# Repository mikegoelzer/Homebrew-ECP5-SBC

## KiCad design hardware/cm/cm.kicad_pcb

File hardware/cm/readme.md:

# Compute Module

The Compute Module (CM) is the heart of the computer.  It has the two things that every computer needs:  a processor and memory.  

### Features

- ECP5U 85K FPGA
- 1.1V, 2.5V and 3.3V buck regulators for the FPGA's voltage rails
- Supply sequencer to bring voltage rails up and down "correctly" (see below)
- 16MB DRAM
- 25MHz oscillator
- Bitstream SPI flash chip
- 100-pin Hirose DF13 snap-in connectors on the bottom

### Power

The Compute Module is powered by a 5V input.  The 1.1V and 2.5V and 3.3V rails are produced by three TI buck regulators.

The ECP5 should not require a rail sequencer, but I included one (based on a design borrowed from Trellis Board) because I've seen other ECP5 boards get into weird states that seem like they may be caused by rail ramp rate problems.  Thus, the rail sequencing complies strictly with the ECP5's datasheet, at a cost of two extra chips.

### Electrical and Mechanical Connections

The basic idea with the CM is that you use it by snapping it into some larger board -- in my case, the [the motherboard](../motherboard/readme.md) in this repo.  This is the purpose of the two 100-pin Hirose DF13 male connectors on the bottom of the CM.  Everything, even power andJTAG, is brought out solely through these connectors.

The connectors and overall size and shape were inspired by the Raspberry Pi Compute Module 3 (CM3).  I wasn't able to maintain the same pinout as the Pi CM3 because I needed to bring out more IOs and wanted to run off a 5V input.

### Clock Speed

The FPGA includes several PLLs, so the 25 MHz oscillator in this circuit enables the CPU to run at 100 MHz.  

While the CPU itself would probably run fine at higher clock speeds, the DRAM is rated for a maximum speed of 133 MHz.  The memory controller is simplified considerably when you can get results back from DRAM in one clock cycle, so I just run everything in a single 100 MHz clock domain.

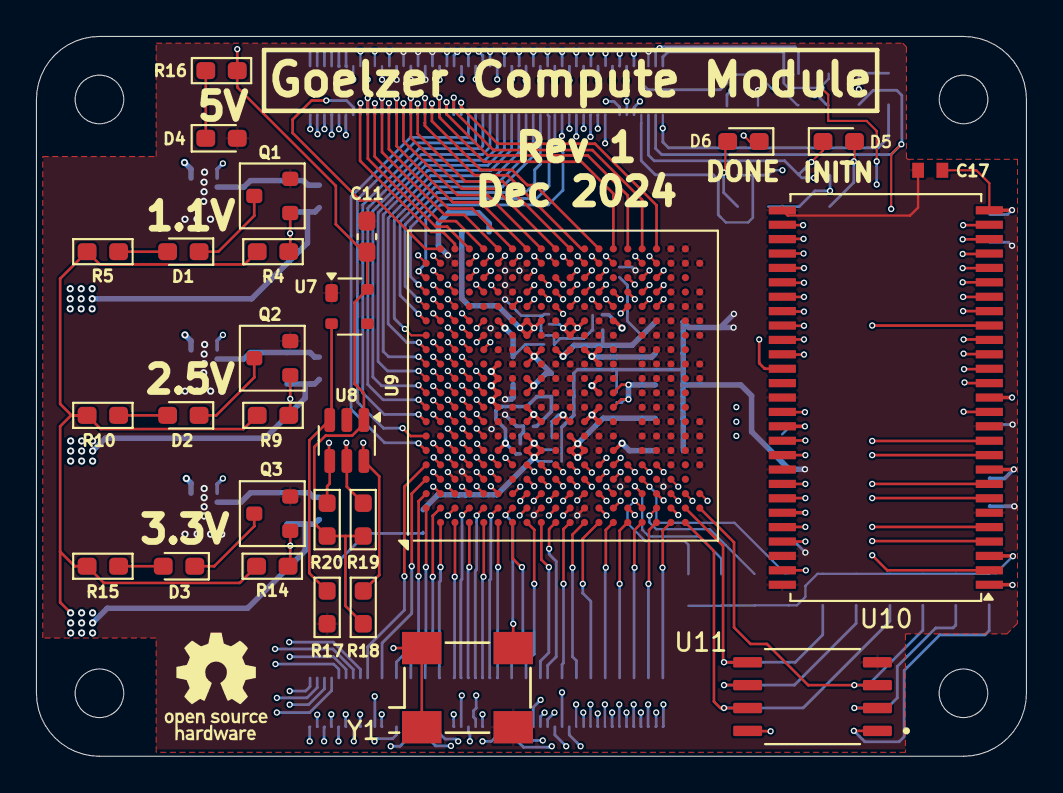
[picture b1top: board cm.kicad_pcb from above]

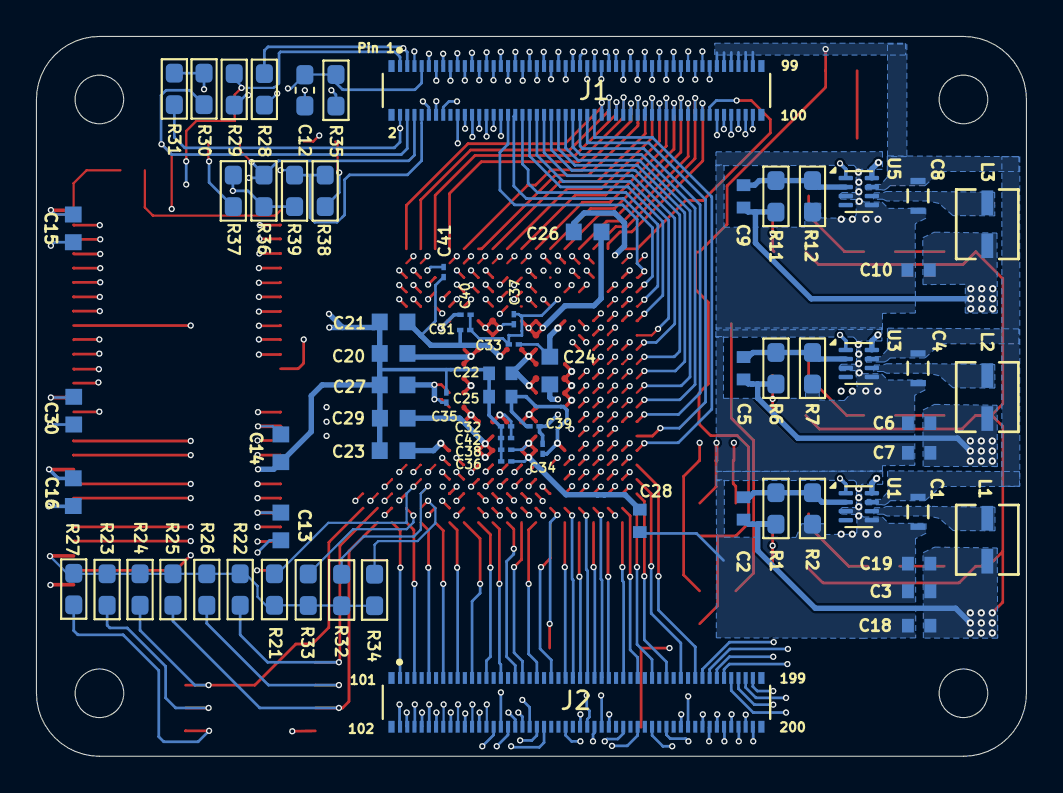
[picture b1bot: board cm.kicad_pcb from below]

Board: 8 copper layers, 55.0 x 40.0 mm, 105 parts (73 on the bottom side), 230 nets.

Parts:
C1, C4, C8: 4.7uF; CAP_1608_TDK-L
C2, C5, C9: 120pF; G-188_MUR-L
C3, C6, C7, C10, C18, C19: 22uF 6.3V; G-188_MUR-L
C11: 0.1uF; C_0603_1608Metric_Pad1.08x0.95mm_HandSolder
C12: 220nF; C_0603_1608Metric_Pad1.08x0.95mm_HandSolder
C13, C14, C15, C16, C20, C21, C23, C24, C26, C27, C29, C30: 22nF; CAPC1608X90N
C17: 2.2uF X5R; CAP_GRM188R61E225KA12D_MUR-L
C22, C25, C28: 2.2uF X7R; G-188_MUR-L
C31, C32, C33, C34, C35, C36, C37, C38, C39, C40, C41, C42: 10nF; G-033_MUR-L
D1, D2, D3, D4, D6: Green; LED_0603_1608Metric_Pad1.05x0.95mm_HandSolder
D5: Red; LED_0603_1608Metric_Pad1.05x0.95mm_HandSolder
H1, H2, H3, H4: MountingHole; MountingHole_2.7mm_M2.5
J1, J2: DF40C-100DP-0.4V_51_; HIROSE_DF40C-100DP-0.4V_51_
L1, L2, L3: 470nH IHLP1212AB; IND_IHLP-1212AB_VIS-L
Q1, Q2, Q3: BSH111; SOT-23
R1: 453k 1%; R_0603_1608Metric_Pad1.05x0.95mm_HandSolder
R2, R7, R12: 100k 1%; R_0603_1608Metric_Pad1.05x0.95mm_HandSolder
R4, R9, R14, R22, R23, R24, R25, R36, R39: 10k; R_0603_1608Metric_Pad1.05x0.95mm_HandSolder
R5, R10, R15, R16, R26: 1k; R_0603_1608Metric_Pad1.05x0.95mm_HandSolder
R6: 316k 1%; R_0603_1608Metric_Pad1.05x0.95mm_HandSolder
R11: 82.5 1%; R_0603_1608Metric_Pad1.05x0.95mm_HandSolder
R17: 100k 1%; R_0603_1608Metric_Pad0.98x0.95mm_HandSolder
R18, R19, R20: 100k; R_0603_1608Metric_Pad0.98x0.95mm_HandSolder
R21, R27, R28, R29, R30, R31, R32, R33, R34, R35: 4.7k; R_0603_1608Metric_Pad1.05x0.95mm_HandSolder
R37, R38: 2.2k; R_0603_1608Metric_Pad1.05x0.95mm_HandSolder
U1, U3, U5: TPS62823DLC; Texas_VSON-HR-8_1.5x2mm_P0.5mm
U7: ADM811MART; SOT-143
U8: LM3880MF-1AA; SOT-23-6
U9: LFE5U-85F-6BG381x; Lattice_caBGA-381_17.0x17.0mm_Layout20x20_P0.8mm_Ball0.4mm_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
U10: MT48LC16M16A2P; TSOP-II-54_22.2x10.16mm_P0.8mm
U11: W25Q128JVSIQ; SOIC127P790X216-8N
Y1: FNETHE025; Crystal_SMD_7050_4Pads

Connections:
+1V1: C9.1, C10.1, C20.1, C21.1, C22.1, C31.1, C32.1, C41.1, C42.1, L3.2, R11.1, U9.H8 (VCC), U9.H9 (VCC), U9.H10 (VCC), U9.H11 (VCC), U9.H12 (VCC), U9.H13 (VCC), U9.J8 (VCC), U9.J13 (VCC), U9.K8 (VCC), U9.K13 (VCC), U9.L8 (VCC), U9.L13 (VCC), U9.M8 (VCC), U9.M13 (VCC), U9.N8 (VCC), U9.N9 (VCC), U9.N10 (VCC), U9.N11 (VCC), U9.N12 (VCC), U9.N13 (VCC)
+2V5: C5.1, C6.1, C7.1, C23.1, C24.1, C25.1, C33.1, C34.1, C39.1, C40.1, L2.2, R6.1, U9.F6 (VCCAUX), U9.F15 (VCCAUX), U9.P6 (VCCAUX), U9.P15 (VCCAUX)
+3V3: C2.1, C3.1, C13.1, C14.1, C15.1, C16.1, C17.1, C18.1, C19.1, C26.1, C27.1, C28.1, C29.1, C30.1, C35.1, C36.1, C37.1, C38.1, D6.1 (K), J1.77, J1.79, J1.81, J1.83, J1.85, J1.87, L1.2, R1.1, R4.2, R5.2, R9.2, R10.2, R14.2, R15.2, R21.2, R22.1, R23.1, R24.1, R25.1, R26.1, R27.2, R29.2, R30.2, R31.2, R32.1, R33.1, R34.1, R35.1, R36.2, R37.2, R39.1, U9.F9 (VCCIO0), U9.F10 (VCCIO0), U9.F11 (VCCIO1), U9.F12 (VCCIO1), U9.H6 (VCCIO7), U9.H7 (VCCIO7), U9.H14 (VCCIO2), U9.H15 (VCCIO2), U9.J6 (VCCIO7), U9.J15 (VCCIO2), U9.L6 (VCCIO6), U9.L7 (VCCIO6), U9.L14 (VCCIO3), U9.L15 (VCCIO3), U9.M6 (VCCIO6), U9.M15 (VCCIO3), U9.P9 (VCCIO8), U9.P10 (VCCIO8), U10.1 (VDD), U10.3 (VDDQ), U10.9 (VDDQ), U10.14 (VDD), U10.27 (VDD), U10.43 (VDDQ), U10.49 (VDDQ), U11.8 (VCC), Y1.1, Y1.4
+5V: C1.1, C4.1, C8.1, C11.1, J1.89, J1.91, J1.93, J1.95, J1.97, J1.99, R16.1, R18.1, R19.1, R20.1, U1.7 (VIN), U3.7 (VIN), U5.7 (VIN), U7.4 (VCC), U8.1 (VCC)
/Flash + JTAG/CS1N: R33.2, U9.U2 (PB13B)
/Flash + JTAG/FLASH_CSN: R27.1, U9.R2 (PB15A), U11.1 (/CS)
/Flash + JTAG/FLASH_IO0: R22.2, U9.W2 (PB11B), U11.5 (DI(IO0))
/Flash + JTAG/FLASH_IO1: R23.2, U9.V2 (PB11A), U11.2 (DO(IO1))
/Flash + JTAG/FLASH_IO2: R24.2, U9.Y2 (PB9B), U11.3 (/WP(IO2))
/Flash + JTAG/FLASH_IO3: R25.2, U9.W1 (PB9A), U11.7 (/HOLD/RESET(IO3))
/Flash + JTAG/FLASH_SCK: R26.2, U9.U3 (CCLK), U11.6 (CLK)
/Flash + JTAG/SN_CSN: R34.2, U9.T2 (PB13A)
/Flash + JTAG/WRITEN: R32.2, U9.T3 (PB18A)
/Hirose Connectors/IO_C2: J2.42, U9.C2 (PL35D)
/Hirose Connectors/IO_C6: J2.22, U9.C6 (PT11A)
/Hirose Connectors/IO_C7: J2.18, U9.C7 (PT11B)
/Hirose Connectors/IO_C8: J2.14, U9.C8 (PT15A)
/Hirose Connectors/IO_C9: J2.10, U9.C9 (PT54A)
/Hirose Connectors/IO_C11: J2.26, U9.C11 (PT65B)
/Hirose Connectors/IO_D3: J2.40, U9.D3 (PL17D)
/Hirose Connectors/IO_D11: J2.6, U9.D11 (PT69A)
/Hirose Connectors/IO_E3: J2.38, U9.E3 (PL20B)
/Hirose Connectors/IO_E7: J1.59, U9.E7 (PT9A)
/Hirose Connectors/IO_F3: J2.28, U9.F3 (PL44B)
/Hirose Connectors/IO_G3: J2.58, U9.G3 (PL44A)
/Hirose Connectors/IO_H2: J2.36, U9.H2 (PL47C)
/Hirose Connectors/IO_H3: J2.54, U9.H3 (PL41D)
/Hirose Connectors/IO_J3: J2.34, U9.J3 (PL50C)
/Hirose Connectors/IO_K2: J2.30, U9.K2 (PL53A)
/Hirose Connectors/IO_K3: J2.32, U9.K3 (PL50D)
/Hirose Connectors/IO_L2: J2.24, U9.L2 (PL86D)
/Hirose Connectors/IO_L3: J2.20, U9.L3 (PL86C)
/Hirose Connectors/IO_M3: J2.16, U9.M3 (PL86B)
/Hirose Connectors/IO_N2: J2.8, U9.N2 (PL89A)
/Hirose Connectors/IO_N3: J2.12, U9.N3 (PL86A)
/Hirose Connectors/IO_N4: J1.14, U9.N4 (PL83C)
/Hirose Connectors/IO_N5: J1.55, U9.N5 (PL83B)
/Hirose Connectors/IO_P1: J2.17, U9.P1 (PL92A)
/Hirose Connectors/IO_P2: J1.10, U9.P2 (PL92B)
/Hirose Connectors/IO_P3: J2.4, U9.P3 (PL92C)
/Hirose Connectors/IO_P4: J1.12, U9.P4 (PL92D)
/Hirose Connectors/IO_P5: J1.51, U9.P5 (PL83D)
/Power/1V1_EN: R18.2, U5.1 (EN), U8.6 (FLAG1)
/Power/1V1_PG: Q3.1 (G), R14.1, U5.8 (PG)
/Power/2V5_EN: R20.2, U3.1 (EN), U8.4 (FLAG3)
/Power/2V5_PG: Q2.1 (G), R9.1, U3.8 (PG)
/Power/3V3_EN: R19.2, U1.1 (EN), U8.5 (FLAG2)
/Power/3V3_PG: Q1.1 (G), R4.1, U1.8 (PG)
/Power/SW_1V1: L3.1, U5.6 (SW)
/Power/SW_2V5: L2.1, U3.6 (SW)
/Power/SW_3V3: L1.1, U1.6 (SW)
CLK_25MHZ: U9.G2 (PL47A), Y1.3
ECP5_DONE: J1.8, R38.2, R39.2, U9.Y3 (DONE)
ECP5_INITN: D5.1 (K), J1.6, R36.1, U9.V3 (~INIT)
ECP5_PRGMN_BTN: C12.1, J1.7, R35.2, U9.W3 (~PROGRAM)
GND: C1.2, C3.2, C4.2, C6.2, C7.2, C8.2, C10.2, C11.2, C12.2, C13.2, C14.2, C15.2, C16.2, C17.2, C18.2, C19.2, C20.2, C21.2, C22.2, C23.2, C24.2, C25.2, C26.2, C27.2, C28.2, C29.2, C30.2, C31.2, C32.2, C33.2, C34.2, C35.2, C36.2, C37.2, C38.2, C39.2, C40.2, C41.2, C42.2, D4.2 (A), J1.5, J1.65, J1.67, J1.69, J1.71, J1.73, J1.75, Q1.2 (S), Q2.2 (S), Q3.2 (S), R2.2, R7.2, R12.2, R17.2, R28.1, U1.3 (AGND), U1.5 (PGND), U3.3 (AGND), U3.5 (PGND), U5.3 (AGND), U5.5 (PGND), U7.1 (GND), U8.2 (GND), U9.B7 (GND), U9.B14 (GND), U9.C19 (GND), U9.D4 (GND), U9.F7 (GND), U9.F8 (GND), U9.F13 (GND), U9.F14 (GND), U9.G4 (GND), U9.G6 (GND), U9.G7 (GND), U9.G8 (GND), U9.G9 (GND), U9.G10 (GND), U9.G11 (GND), U9.G12 (GND), U9.G13 (GND), U9.G14 (GND), U9.G15 (GND), U9.G17 (GND), U9.H19 (GND), U9.J2 (GND), U9.J7 (GND), U9.J9 (GND), U9.J10 (GND), U9.J11 (GND), U9.J12 (GND), U9.J14 (GND), U9.K6 (GND), U9.K7 (GND), U9.K9 (GND), U9.K10 (GND), U9.K11 (GND), U9.K12 (GND), U9.K14 (GND), U9.K15 (GND), U9.L9 (GND), U9.L10 (GND), U9.L11 (GND), U9.L12 (GND), U9.M2 (GND), U9.M7 (GND), U9.M9 (GND), U9.M10 (GND), U9.M11 (GND), U9.M12 (GND), U9.M14 (GND), U9.M16 (GND), U9.N6 (GND), U9.N7 (GND), U9.N14 (GND), U9.N15 (GND), U9.P7 (GND), U9.P8 (GND), U9.P11 (GND), U9.P12 (GND), U9.P13 (GND), U9.P14 (GND), U9.R4 (CFG_2), U9.R19 (GND), U9.T6 (GND), U9.T7 (GND), U9.T8 (GND), U9.T9 (GND), U9.T10 (GND), U9.T11 (GND), U9.T12 (GND), U9.T13 (GND), U9.T14 (GND), U9.T15 (GND), U9.U4 (CFG_0), U9.U6 (GND), U9.U7 (GND), U9.U8 (GND), U9.U9 (GND), U9.U10 (GND), U9.U11 (GND), U9.U12 (GND), U9.U13 (GND), U9.U14 (GND), U9.U15 (GND), U9.V5 (GND), U9.V6 (GND), U9.V7 (GND), U9.V8 (GND), U9.V9 (GND), U9.V10 (GND), U9.V11 (GND), U9.V12 (GND), U9.V13 (GND), U9.V14 (GND), U9.V15 (GND), U9.V16 (GND), U9.V17 (GND), U9.V18 (GND), U9.V19 (GND), U9.V20 (GND), U9.W6 (GND), U9.W7 (GND), U9.W12 (GND), U9.W15 (GND), U9.W16 (GND), U9.W19 (GND), U9.W20 (GND), U9.Y5 (GND), U9.Y6 (GND), U9.Y7 (GND), U9.Y8 (GND), U9.Y11 (GND), U9.Y12 (GND), U9.Y14 (GND), U9.Y15 (GND), U9.Y16 (GND), U9.Y17 (GND), U9.Y19 (GND), U10.6 (VSSQ), U10.12 (VSSQ), U10.28 (VSS), U10.41 (VSS), U10.46 (VSSQ), U10.52 (VSSQ), U10.54 (VSS), U11.4 (GND), Y1.2
IO_A2: J2.71, U9.A2 (PL35A)
IO_A3: J2.75, U9.A3 (PL14C)
IO_A4: J2.79, U9.A4 (PL11A)
IO_A5: J2.83, U9.A5 (PL11B)
IO_A6: J1.56, U9.A6 (PT4A)
IO_A7: J1.54, U9.A7 (PT18A)
IO_A8: J1.52, U9.A8 (PT18B)
IO_A9: J1.50, U9.A9 (PT60A)
IO_A10: J1.48, U9.A10 (PT63A)
IO_A11: J1.46, U9.A11 (PT63B)
IO_A12: J1.44, U9.A12 (PT76A)
IO_A13: J1.42, U9.A13 (PT76B)
IO_A14: J1.40, U9.A14 (PT83A)
IO_A15: J1.38, U9.A15 (PT103A)
IO_A16: J1.36, U9.A16 (PT110A)
IO_A17: J1.34, U9.A17 (PT116A)
IO_A18: J1.32, U9.A18 (PT119A)
IO_A19: J1.100, U9.A19 (PT121A)
IO_B1: J2.63, U9.B1 (PL35B)
IO_B2: J2.67, U9.B2 (PL35C)
IO_B3: J2.52, U9.B3 (PL14D)
IO_B4: J2.90, U9.B4 (PL14B)
IO_B5: J2.64, U9.B5 (PL11C)
IO_B6: J1.41, U9.B6 (PT4B)
IO_B8: J1.39, U9.B8 (PT15B)
IO_B9: J1.37, U9.B9 (PT58A)
IO_B10: J1.35, U9.B10 (PT60B)
IO_B11: J1.33, U9.B11 (PT65A)
IO_B12: J1.31, U9.B12 (PT71A)
IO_B13: J1.29, U9.B13 (PT78A)
IO_B15: J1.27, U9.B15 (PT105A)
IO_B16: J1.25, U9.B16 (PT110B)
IO_B17: J1.23, U9.B17 (PT114A)
IO_B18: J1.21, U9.B18 (PT116B)
IO_B19: J1.98, U9.B19 (PT119B)
IO_B20: J1.88, U9.B20 (PT121B)
IO_C1: J2.59, U9.C1 (PL38A)
IO_C3: J2.48, U9.C3 (PL17C)
IO_C4: J2.88, U9.C4 (PL14A)
IO_C5: J2.94, U9.C5 (PL11D)
IO_C10: J2.2, U9.C10 (PT58B)
IO_C12: J1.9, U9.C12 (PT71B)
IO_C13: J1.11, U9.C13 (PT78B)
IO_C14: J1.13, U9.C14 (PT83B)
IO_C15: J1.15, U9.C15 (PT105B)
IO_C16: J1.17, U9.C16 (PT112A)
IO_C17: J1.19, U9.C17 (PT114B)
IO_C20: J1.86, U9.C20 (PR35A)
IO_D1: J2.55, U9.D1 (PL38B)
IO_D2: J2.57, U9.D2 (PL38C)
IO_D5: J2.68, U9.D5 (PL17B)
IO_D6: J2.72, U9.D6 (PT6B)
IO_D7: J2.96, U9.D7 (PT9B)
IO_D8: J2.100, U9.D8 (PT13B)
IO_D9: J2.95, U9.D9 (PT20A)
IO_D10: J2.99, U9.D10 (PT56A)
IO_D12: J1.96, U9.D12 (PT74A)
IO_D13: J1.94, U9.D13 (PT80A)
IO_D14: J1.90, U9.D14 (PT85A)
IO_D15: J1.92, U9.D15 (PT107A)
IO_D18: J1.28, U9.D18 (PR14A)
IO_D19: J1.26, U9.D19 (PR35B)
IO_D20: J1.84, U9.D20 (PR35C)
IO_E1: J2.51, U9.E1 (PL38D)
IO_E2: J2.53, U9.E2 (PL44D)
IO_E4: J2.86, U9.E4 (PL17A)
IO_E5: J2.80, U9.E5 (PL20C)
IO_E6: J2.76, U9.E6 (PT6A)
IO_E8: J2.98, U9.E8 (PT13A)
IO_E9: J2.85, U9.E9 (PT20B)
IO_E10: J2.93, U9.E10 (PT56B)
IO_E11: J2.97, U9.E11 (PT69B)
IO_E13: J2.89, U9.E13 (PT80B)
IO_E14: J2.87, U9.E14 (PT85B)
IO_E15: J2.91, U9.E15 (PT107B)
IO_E17: J1.30, U9.E17 (PR14B)
IO_E18: J1.24, U9.E18 (PR14C)
IO_E19: J1.22, U9.E19 (PR35D)
IO_E20: J1.82, U9.E20 (PR38A)
IO_F1: J2.47, U9.F1 (PL47B)
IO_F2: J2.49, U9.F2 (PL44C)
IO_F4: J2.56, J2.82, U9.F4 (PL20A)
IO_F5: J2.92, U9.F5 (PL20D)
IO_F17: J1.20, U9.F17 (PR17A)
IO_F19: J1.18, U9.F19 (PR38B)
IO_F20: J1.80, U9.F20 (PR38C)
IO_G1: J2.43, U9.G1 (PL47D)
IO_G5: J2.60, U9.G5 (PL41B)
IO_G20: J1.78, U9.G20 (PR38D)
IO_H1: J2.39, U9.H1 (PL53C)
IO_H20: J1.76, U9.H20 (PR41B)
IO_J1: J2.35, U9.J1 (PL53B)
IO_J19: J1.63, U9.J19 (PR44A)
IO_J20: J1.74, U9.J20 (PR44C)
IO_K1: J2.33, U9.K1 (PL53D)
IO_K19: J1.61, U9.K19 (PR44B)
IO_K20: J1.72, U9.K20 (PR44D)
IO_L1: J2.29, U9.L1 (PL89C)
IO_L19: J1.57, U9.L19 (PR47C)
IO_L20: J1.70, U9.L20 (PR47A)
IO_M1: J2.25, U9.M1 (PL89B)
IO_M19: J1.53, U9.M19 (PR47D)
IO_M20: J1.68, U9.M20 (PR47B)
IO_N1: J2.21, U9.N1 (PL89D)
IO_N19: J1.49, U9.N19 (PR83A)
IO_N20: J1.66, U9.N20 (PR83B)
IO_P19: J1.47, U9.P19 (PR83C)
IO_P20: J1.64, U9.P20 (PR86A)
IO_R1: J2.13, U9.R1 (PB4A)
IO_R20: J1.62, U9.R20 (PR86B)
IO_T1: J2.9, U9.T1 (PB4B)
IO_T19: J1.45, U9.T19 (PR89A)
IO_T20: J1.60, U9.T20 (PR86C)
IO_U1: J2.5, U9.U1 (PB6A)
IO_U19: J1.43, U9.U19 (PR89C)
IO_U20: J1.58, U9.U20 (PR86D)
IO_V1: J2.1, U9.V1 (PB6B)
JTAG_TCK: J1.3, R28.2, U9.T5 (TCK)
JTAG_TDI: J1.4, R30.1, U9.R5 (TDI)
JTAG_TDO: J1.1, R29.1, U9.V4 (TDO)
JTAG_TMS: J1.2, R31.1, U9.U5 (TMS)
unnamed: D1.2 (A), R5.1
unnamed: D1.1 (K), Q1.3 (D)
unnamed: D2.2 (A), R10.1
unnamed: D2.1 (K), Q2.3 (D)
unnamed: D3.2 (A), R15.1
unnamed: D3.1 (K), Q3.3 (D)
unnamed: D4.1 (K), R16.2
unnamed: D5.2 (A), R37.1
unnamed: D6.2 (A), R38.1
unnamed: C2.2, R1.2, R2.1, U1.2 (FB)
unnamed: C5.2, R6.2, R7.1, U3.2 (FB)
unnamed: C9.2, R11.2, R12.1, U5.2 (FB)
unnamed: R17.1, U7.2 (~RESET), U8.3 (EN)
unnamed: R21.1, U9.T4 (CFG_1)
SDRAM_A0: U9.G19 (PR41A), U10.23 (A0)
SDRAM_A1: U9.U16 (PR92C), U10.24 (A1)
SDRAM_A2: U9.U17 (PR92B), U10.25 (A2)
SDRAM_A3: U9.U18 (PR92A), U10.26 (A3)
SDRAM_A4: U9.T18 (PR89D), U10.29 (A4)
SDRAM_A5: U9.T17 (PR92D), U10.30 (A5)
SDRAM_A6: U9.T16 (PR77A), U10.31 (A6)
SDRAM_A7: U9.G16 (PR17C), U10.32 (A7)
SDRAM_A8: U9.H17 (PR20B), U10.33 (A8)
SDRAM_A9: U9.J18 (PR41C), U10.34 (A9)
SDRAM_A10: U9.H18 (PR20A), U10.22 (A10)
SDRAM_A11: U9.P17 (PR53D), U10.35 (A11)
SDRAM_A12: U9.R16 (PR56C), U10.36 (A12)
SDRAM_BA0: U9.J17 (PR20C), U10.20 (BA0)
SDRAM_BA1: U9.H16 (PR17D), U10.21 (BA1)
SDRAM_CASN: U9.K17 (PR29B), U10.17 (~CAS)
SDRAM_CKE: U9.R18 (PR89B), U10.37 (CKE)
SDRAM_CLK: U9.R17 (PR56D), U10.38 (CLK)
SDRAM_CSN: U9.P16 (PR56B), U10.19 (~CS)
SDRAM_D0: U9.M4 (PL83A), U10.2 (DQ0)
SDRAM_D1: U9.N17 (PR56A), U10.4 (DQ1)
SDRAM_D2: U9.N18 (PR53C), U10.5 (DQ2)
SDRAM_D3: U9.M18 (PR50D), U10.7 (DQ3)
SDRAM_D4: U9.L18 (PR50C), U10.8 (DQ4)
SDRAM_D5: U9.M17 (PR53B), U10.10 (DQ5)
SDRAM_D6: U9.N16 (PR53A), U10.11 (DQ6)
SDRAM_D7: U9.L17 (PR50B), U10.13 (DQ7)
SDRAM_D8: U9.H5 (PL41C), U10.42 (DQ8)
SDRAM_D9: U9.J4 (PL50A), U10.44 (DQ9)
SDRAM_D10: U9.J5 (PL50B), U10.45 (DQ10)
SDRAM_D11: U9.K4 (PL56A), U10.47 (DQ11)
SDRAM_D12: U9.K5 (PL56B), U10.48 (DQ12)
SDRAM_D13: U9.L4 (PL56C), U10.50 (DQ13)
SDRAM_D14: U9.L5 (PL56D), U10.51 (DQ14)
SDRAM_D15: U9.M5 (PL77A), U10.53 (DQ15)
SDRAM_DQM0: U9.L16 (PR50A), U10.15 (DQML)
SDRAM_DQM1: U9.H4 (PL41A), U10.39 (DQMH)
SDRAM_RASN: U9.K16 (PR29A), U10.18 (~RAS)
SDRAM_WEN: U9.K18 (PR41D), U10.16 (~WE)

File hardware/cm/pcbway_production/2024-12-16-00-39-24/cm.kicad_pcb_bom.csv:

Designator,Quantity,Value,Footprint,Package,MPN,DNP,Mount_Type,Description,Digikey,Mfgr,PARTREV,STANDARD,MAXIMUM_PACKAGE_HEIGHT,MANUFACTURER,Mouser
"C1, C4, C8",3,4.7uF,CAP_1608_TDK-L,,C1608X6S1C475K080AC,,smt,CAP CER 4.7UF 16V X6S 0603,https://www.digikey.com/en/products/detail/tdk-corporation/C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,TDK,,,,,
"C10, C18, C19, C3, C6, C7",6,22uF 6.3V,G-188_MUR-L,,GRM188R60J226MEA0D,,smt,CAP CER 22UF 6.3V X5R 0603,https://www.digikey.com/en/products/detail/murata-electronic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,Murata Electronics,,,,,
C11,1,0.1uF,C_0603_1608Metric_Pad1.08x0.95mm_HandSolder,,GRM188R72A104KA35D,,smt,Unpolarized capacitor,https://www.digikey.com/en/products/detail/murata-electronic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,Murata,,,,,
C12,1,220nF,C_0603_1608Metric_Pad1.08x0.95mm_HandSolder,,CC0603KRX5R5BB224,,smt,CAP CER 0.22UF 6.3V X5R 0603,https://www.digikey.com/en/products/detail/yageo/CC0603KRX5R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,YAGEO,,,,,
"C13, C14, C15, C16, C20, C21, C23, C24, C26, C27, C29, C30",12,22nF,CAPC1608X90N,,GCM188R72A223KA37J,,smt,CAP CER 0.022UF 100V X7R 0603,https://www.digikey.com/en/products/detail/murata-electronic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,Murata Electronics,,,,,
C17,1,2.2uF X5R,CAP_GRM188R61E225KA12D_MUR-L,,GRM188R61E225KA12D,,smt,CAP CER 2.2UF 25V X5R 0603,https://www.digikey.com/en/products/detail/murata-electronic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,Murata Electronics,,,,,
"C2, C5, C9",3,120pF,G-188_MUR-L,,GRM1885C1H121JA01D,,smt,CAP CER 120PF 50V C0G/NP0 0603,https://www.digikey.com/en/products/detail/murata-electronic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,Murata,,,,,
"C22, C25, C28",3,2.2uF X7R,G-188_MUR-L,,GRM188R71A225KE15D,,smt,CAP CER 2.2UF 10V X7R 0603,https://www.digikey.com/en/products/detail/murata-electronic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,Murata Electronics,,,,,
"C31, C32, C33, C34, C35, C36, C37, C38, C39, C40, C41, C42",12,10nF,G-033_MUR-L,,GRM033R71A103KA01D,,smt,CAP CER 10000PF 10V X7R 0201,https://www.digikey.com/en/products/detail/murata-electronic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,Murata Electronics,,,,,
"D1, D2, D3, D4, D6",5,Green,LED_0603_1608Metric_Pad1.05x0.95mm_HandSolder,,150060VS75000,,smt,Light emitting diode,https://www.digikey.com/en/products/detail/w%C3%BCrth-elektr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,Wurth,,,,,
D5,1,Red,LED_0603_1608Metric_Pad1.05x0.95mm_HandSolder,,150060SS75000,,smt,Light emitting diode,https://www.digikey.com/en/products/detail/w%C3%BCrth-elektr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,Wurth,,,,,
"H1, H2, H3, H4",4,MountingHole,MountingHole_2.7mm_M2.5,,,,tht,Mounting Hole without connection,,,,,,,
"J1, J2",2,DF40C-100DP-0.4V_51_,HIROSE_DF40C-100DP-0.4V_51_,,,,smt,"Hirose DF40 1.5mm stacked, plug (male)",,,8,Manufacturer Recommendations,1.29mm,Hirose,
"L1, L2, L3",3,470nH IHLP1212AB,IND_IHLP-1212AB_VIS-L,,IHLP1212ABERR47M11,,smt,FIXED IND 470NH 6.4A 19.5MOHM SMD,https://www.digikey.com/en/products/detail/vishay-dale/IHLP1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,Vishay Dale,,,,,
"Q1, Q2, Q3",3,BSH111,SOT-23,,BSH111BKR,,smt,"SOT-23 N-MOSFET enchancement mode transistor, 55V, 210mA, 302mW, Alternate KiCAD Library",https://www.digikey.com/en/products/detail/nexperia-usa-inc/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,Nexperia,,,,,
R1,1,453k 1%,R_0603_1608Metric_Pad1.05x0.95mm_HandSolder,,RC0603FR-07453KL,,smt,RES 453K OHM 1% 1/10W 0603,https://www.digikey.com/en/products/detail/yageo/RC0603FR-07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,YAGEO,,,,,
"R10, R15, R16, R26, R5",5,1k,R_0603_1608Metric_Pad1.05x0.95mm_HandSolder,,RC0603FR-071KL,,smt,"Resistor, US symbol",[R5]https://www.digikey.com/en/products/detail/yageo/RC0603FR-07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; [R26]https://www.digikey.com/en/products/detail/yageo/rc0603fr-07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,YAGEO,,,,,
R11,1,82.5 1%,R_0603_1608Metric_Pad1.05x0.95mm_HandSolder,,RC0603FR-0782K5L,,smt,RES 82.5K OHM 1% 1/10W 0603,https://www.digikey.com/en/products/detail/yageo/rc0603fr-07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,YAGEO,,,,,
"R12, R2, R7",3,100k 1%,R_0603_1608Metric_Pad1.05x0.95mm_HandSolder,,RC0603FR-07100KL,,smt,RES 100K OHM 1% 1/10W 0603,https://www.digikey.com/en/products/detail/yageo/RC0603FR-07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,YAGEO,,,,,
"R14, R22, R23, R24, R25, R36, R39, R4, R9",9,10k,R_0603_1608Metric_Pad1.05x0.95mm_HandSolder,,RC0603FR-0710KL,,smt,"Resistor, US symbol",https://www.digikey.com/en/products/detail/yageo/RC0603FR-07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,YAGEO,,,,,
R17,1,100k 1%,R_0603_1608Metric_Pad0.98x0.95mm_HandSolder,,RC0603FR-07100KL,,smt,RES 100K OHM 1% 1/10W 0603,https://www.digikey.com/en/products/detail/yageo/RC0603FR-07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,YAGEO,,,,,
"R18, R19, R20",3,100k,R_0603_1608Metric_Pad0.98x0.95mm_HandSolder,,RC0603FR-07100KL,,smt,RES 100K OHM 1% 1/10W 0603,https://www.digikey.com/en/products/detail/yageo/RC0603FR-07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,YAGEO,,,,,
"R21, R27, R28, R29, R30, R31, R32, R33, R34, R35",10,4.7k,R_0603_1608Metric_Pad1.05x0.95mm_HandSolder,,RC0603FR-074K7L,,smt,"Resistor, US symbol",https://www.digikey.com/en/products/detail/yageo/rc0603fr-07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,YAGEO,,,,,
"R37, R38",2,2.2k,R_0603_1608Metric_Pad1.05x0.95mm_HandSolder,,RC0603FR-072K2L,,smt,"Resistor, US symbol",https://www.digikey.com/en/products/detail/yageo/RC0603FR-07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,YAGEO,,,,,
R6,1,316k 1%,R_0603_1608Metric_Pad1.05x0.95mm_HandSolder,,RC0603FR-07316KL,,smt,RES 316K OHM 1% 1/10W 0603,https://www.digikey.com/en/products/detail/yageo/rc0603fr-07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,YAGEO,,,,,
"U1, U3, U5",3,TPS62823DLC,Texas_VSON-HR-8_1.5x2mm_P0.5mm,,TPS62823DLCR,,smt,"3A Step-Down Converter with DCS-Control, adjustable output, 2.4-5.5V input voltage, QFN-8",https://www.digikey.com/en/products/detail/texas-instruments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,Texas Instruments,,,,,
U10,1,MT48LC16M16A2P,TSOP-II-54_22.2x10.16mm_P0.8mm,,,,smt,"256M – (16M x 16 bit) Synchronous DRAM (SDRAM), TSOP-II-54",https://www.digikey.com/en/products/detail/micron-technology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,,,,,,https://www.mouser.com/ProductDetail/Micron/MT48LC16M16A2P-6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
U11,1,W25Q128JVSIQ,SOIC127P790X216-8N,,,,smt,,,,I,IPC-7351B,2.16 mm,Winbond Electronics,
U7,1,ADM811MART,SOT-143,,ADM811MARTZ-REEL7,,smt,"Power supply supervisor, Manual reset, Threshold 4.38V, SOT-143",https://www.digikey.com/en/products/detail/analog-devices-in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,Analog Devices,,,,,
U8,1,LM3880MF-1AA,SOT-23-6,,LM3880MFX-1AA/NOPB,,smt,"Simple Power Sequencer, SOT-23-6",https://www.digikey.com/en/products/detail/texas-instruments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,Texas Instruments,,,,,
U9,1,LFE5U-85F-6BG381x,Lattice_caBGA-381_17.0x17.0mm_Layout20x20_P0.8mm_Ball0.4mm_Pad0.4mm_NSMD,,,,smt,"ECP5 FPGA, 84K LUTs, 1.2V, BGA-381",,,,,,,
Y1,1,FNETHE025,Crystal_SMD_7050_4Pads,,FNETHE025,,smt,XTAL OSC XO 25.0000MHZ CMOS SMD,https://www.digikey.com/en/products/detail/diodes-incorporat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,Diodes Incorporated,,,,,

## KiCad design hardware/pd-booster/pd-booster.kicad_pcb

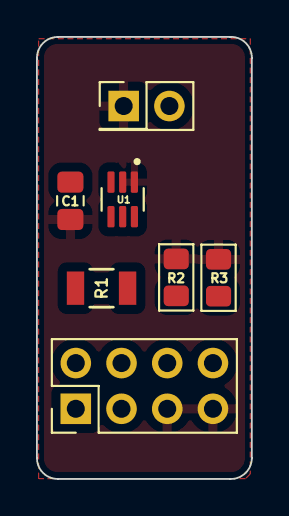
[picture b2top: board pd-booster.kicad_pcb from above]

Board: 2 copper layers, 11.9 x 24.6 mm, 7 parts (0 on the bottom side), 6 nets, no tracks yet.

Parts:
C1: 0.1uF; C_0805_2012Metric_Pad1.18x1.45mm_HandSolder
J1: 2x4 male 0.1"; PinHeader_2x04_P2.54mm_Vertical
J2: PH1RB-02-UA; PinHeader_2x01_P2.54mm_Vertical
R1: 2mΩ 1% 1W; STA_CSNL1206_STP
R2, R3: 5.1k 1%; R_0805_2012Metric_Pad1.15x1.40mm_HandSolder
U1: INA211BIDCKT; SOT65P210X110-6N

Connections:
/5V_OUT: J1.3, J1.4, R1.2, U1.5 (-IN)
/CC1: J1.6, R2.1
/CC2: J1.8, R3.1
/ISENSE: J2.2, U1.6 (OUT)
/VBUS_IN: C1.1, J1.1, J1.2, R1.1, U1.3 (V+), U1.4 (+IN)
GND: C1.2, J1.5, J1.7, J2.1, R2.2, R3.2, U1.1 (REF), U1.2 (GND)

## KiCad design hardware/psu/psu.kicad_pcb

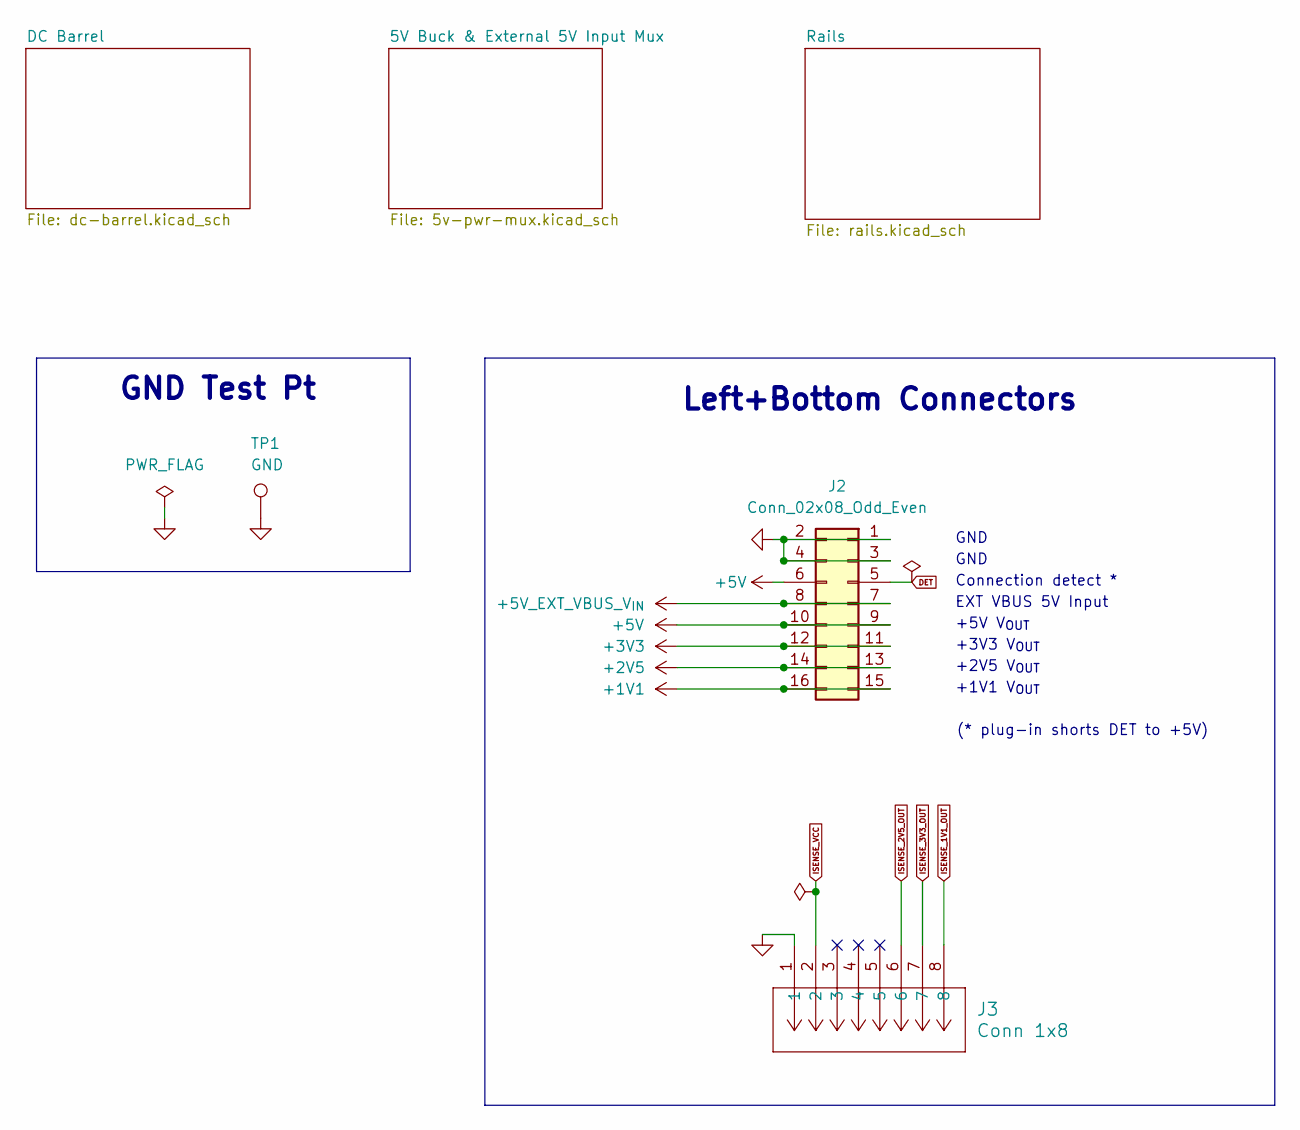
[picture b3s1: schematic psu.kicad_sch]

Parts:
J2: Conn_02x08_Odd_Even; PinSocket_2x08_P2.54mm_Vertical
J3: Conn 1x8; CONN8_61300811121_WRE; MPN 61300811121
TP1: GND; TestPoint_Keystone_5000-5004_Miniature; MPN 5001

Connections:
+1V1: J2.15, J2.16; also elsewhere on the board
+2V5: J2.13, J2.14; also elsewhere on the board
+3V3: J2.11, J2.12; also elsewhere on the board
+5V: J2.6, J2.9, J2.10; also elsewhere on the board
+5V_EXT_VBUS_V_{IN}: J2.7, J2.8; also elsewhere on the board
DET: J2.5; also elsewhere on the board
GND: J2.1, J2.2, J2.3, J2.4, J3.1, TP1.1; also elsewhere on the board
ISENSE_1V1_OUT: J3.8; also elsewhere on the board
ISENSE_2V5_OUT: J3.6; also elsewhere on the board
ISENSE_3V3_OUT: J3.7; also elsewhere on the board
ISENSE_VCC: J3.2; also elsewhere on the board

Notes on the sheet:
GND
Connection detect *
+2V5 V_{OUT}
+5V V_{OUT}
+3V3 V_{OUT}
EXT VBUS 5V Input
(* plug-in shorts DET to +5V)
GND Test Pt
+1V1 V_{OUT}
Left+Bottom Connectors

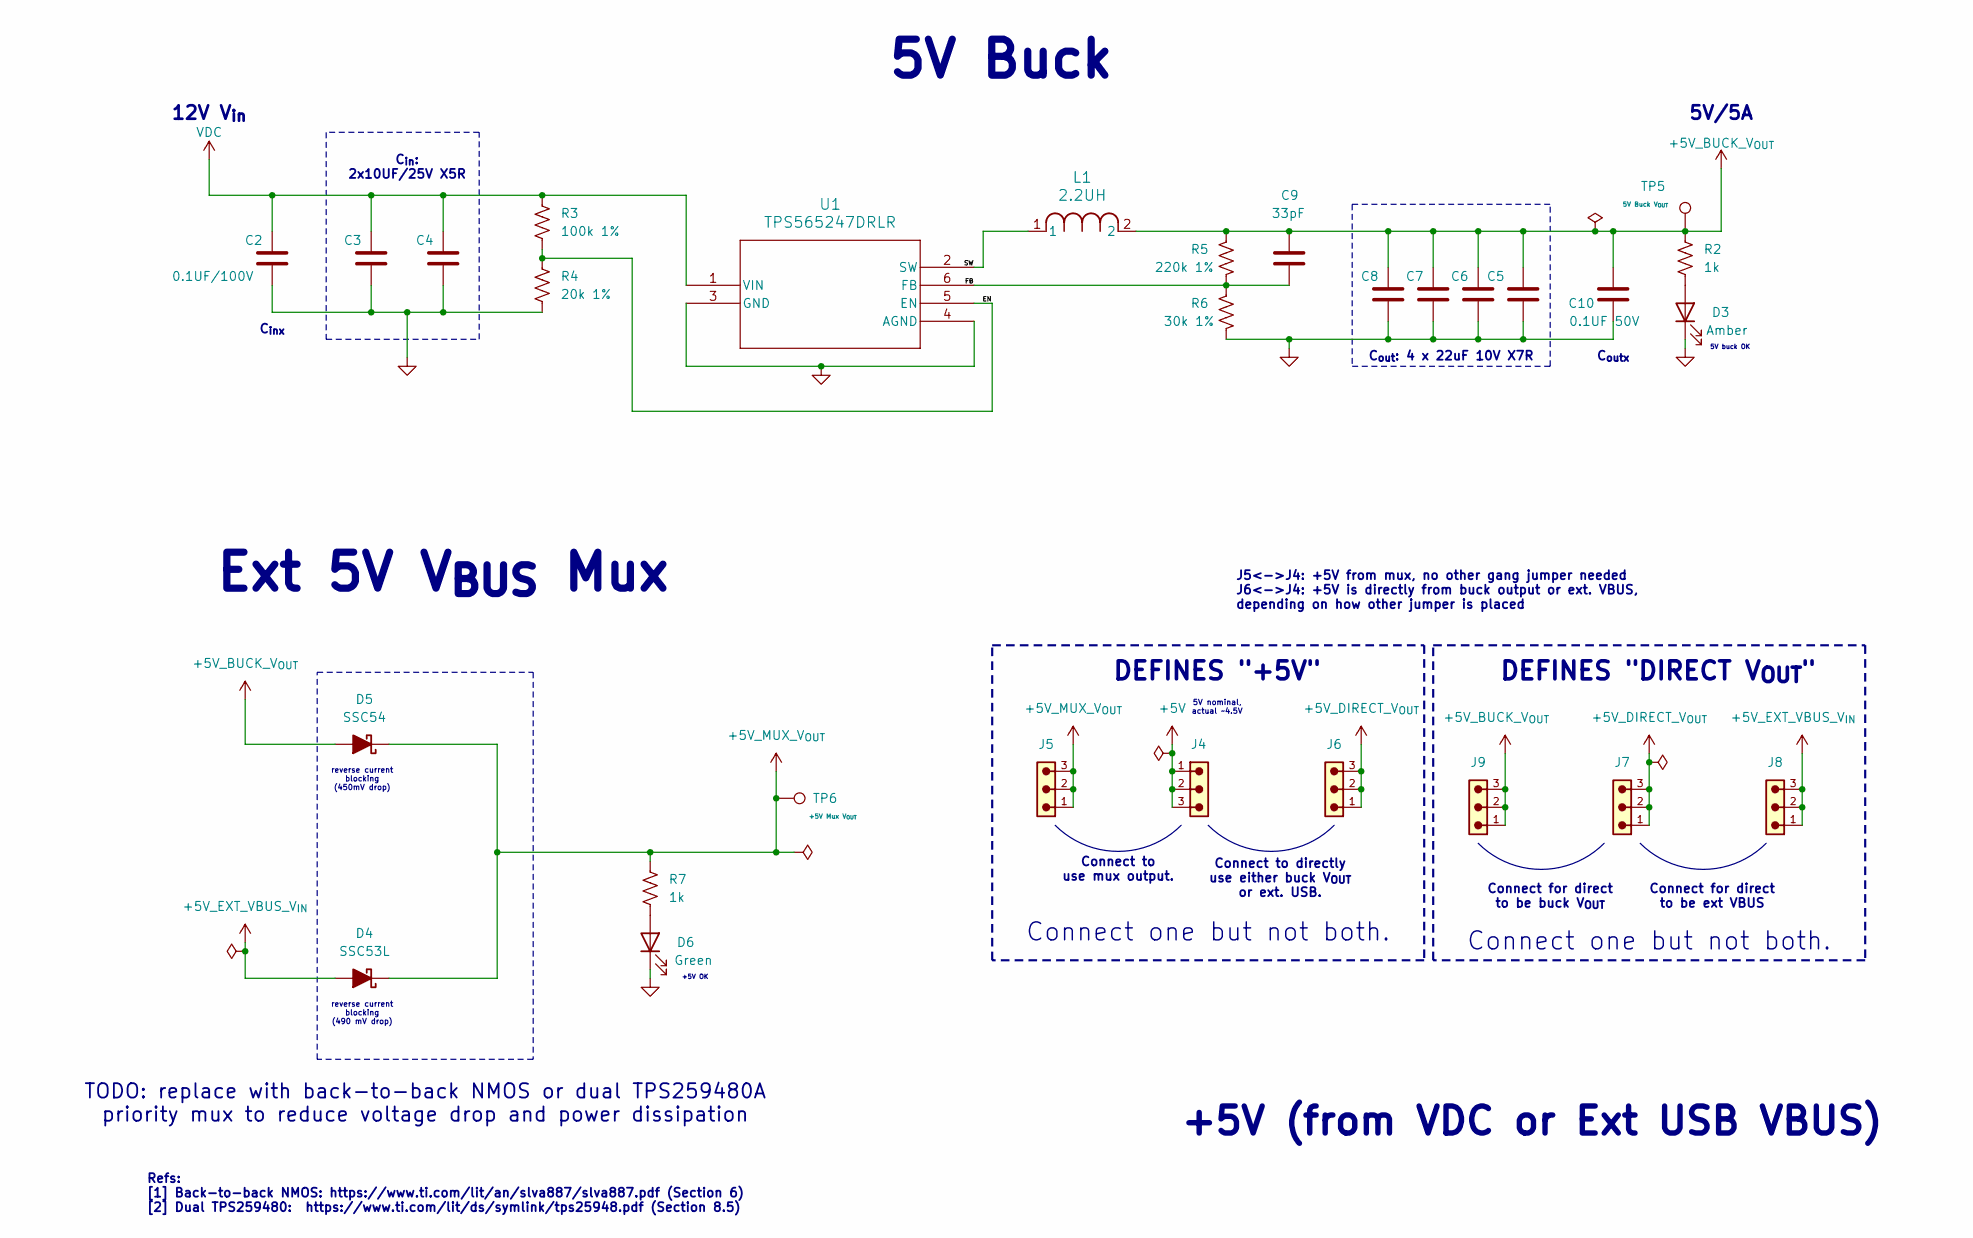
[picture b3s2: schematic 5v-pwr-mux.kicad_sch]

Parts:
C2: 0.1UF/100V; C_0603_1608Metric_Pad1.08x0.95mm_HandSolder; MPN GRM188R72A104KA35D
C3, C4: 10UF 25V X5R; C_0805_2012Metric_Pad1.18x1.45mm_HandSolder; MPN GRM21BR61E106MA73L
C5, C6, C7, C8: 22uF 10V X7R; C_1206_3216Metric_Pad1.33x1.80mm_HandSolder; MPN GRM31CR71A226KE15L
C9: 33pF; C_0402_1005Metric_Pad0.74x0.62mm_HandSolder; MPN GRM1555C1H330JA01D
C10: 0.1UF 50V; C_0603_1608Metric_Pad1.08x0.95mm_HandSolder; MPN GCM188R71H104KA57D
D3: Amber; LED_0603_1608Metric_Pad1.05x0.95mm_HandSolder; MPN 150060AS75000
D4: SSC53L; D_SMC; MPN SSC53L-E3/57T
D5: SSC54; D_SMC; MPN SSC54-E3/57T
D6: Green; LED_0603_1608Metric_Pad1.05x0.95mm_HandSolder; MPN 150060VS75000
J4: +5V; 61300311121; PART-NUMBER 61300311121
J5: +5V_MUX_V_{OUT}; 61300311121; PART-NUMBER 61300311121
J6, J7: +5V_DIRECT_V_{OUT}; 61300311121; PART-NUMBER 61300311121
J8: +5V_EXT_VBUS_V_{IN}; 61300311121; PART-NUMBER 61300311121
J9: +5V_BUCK_V_{OUT}; 61300311121; PART-NUMBER 61300311121
L1: 2.2UH; IND_IHLP-3232DZ_VIS; MPN IHLP3232DZER2R2M11
R2, R7: 1k; R_0603_1608Metric_Pad1.05x0.95mm_HandSolder; MPN RC0603FR-071KL
R3: 100k 1%; R_0603_1608Metric_Pad0.98x0.95mm_HandSolder; MPN RC0603FR-07100KL
R4: 20k 1%; R_0603_1608Metric_Pad0.98x0.95mm_HandSolder; MPN RC0603FR-0720KL
R5: 220k 1%; R_0603_1608Metric_Pad0.98x0.95mm_HandSolder; MPN RC0603FR-07220KL
R6: 30k 1%; R_0603_1608Metric_Pad0.98x0.95mm_HandSolder; MPN RC0603FR-0730KL
TP5: 5V Buck V_{OUT}; TestPoint_Keystone_5000-5004_Miniature; MPN 5000
TP6: +5V Mux V_{OUT}; TestPoint_Keystone_5000-5004_Miniature; MPN 5000
U1: TPS565247DRLR; SOT5X3-6_DRL_TEX; MPN TPS565247DRLR

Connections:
+5V: J4.1, J4.2, J4.3; also elsewhere on the board
+5V_BUCK_V_{OUT}: C5.1, C6.1, C7.1, C8.1, C9.1, C10.1, D5.2 (A), J9.1, J9.2, J9.3, L1.2, R2.1, R5.1, TP5.1
+5V_DIRECT_V_{OUT}: J6.1, J6.2, J6.3, J7.1, J7.2, J7.3
+5V_EXT_VBUS_V_{IN}: D4.2 (A), J8.1, J8.2, J8.3; also elsewhere on the board
+5V_MUX_V_{OUT}: D4.1 (K), D5.1 (K), J5.1, J5.2, J5.3, R7.1, TP6.1
/5V Buck & External 5V Input Mux/EN: R3.2, R4.1, U1.5 (EN)
/5V Buck & External 5V Input Mux/FB: C9.2, R5.2, R6.1, U1.6 (FB)
/5V Buck & External 5V Input Mux/SW: L1.1, U1.2 (SW)
GND: C2.2, C3.2, C4.2, C5.2, C6.2, C7.2, C8.2, C10.2, D3.1 (K), D6.1 (K), R4.2, R6.2, U1.3 (GND), U1.4 (AGND); also elsewhere on the board
unnamed: D3.2 (A), R2.2
unnamed: D6.2 (A), R7.2
VDC: C2.1, C3.1, C4.1, R3.1, U1.1 (VIN); also elsewhere on the board

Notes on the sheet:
+5V (from VDC or Ext USB VBUS)
TODO: replace with back-to-back NMOS or dual TPS259480A priority mux to reduce voltage drop and power dissipation
C_{inx}
DEFINES "+5V"
Connect for direct to be buck V_{OUT}
5V/5A
5V Buck
Refs: [1] Back-to-back NMOS: https://www.ti.com/lit/an/slva887/slva887.pdf (Section 6) [2] Dual TPS259480: https://www.ti.com/lit/ds/symlink/tps25948.pdf (Section 8.5)
12V V_{in}
5V buck OK
C_{outx}
C_{in}: 2x10UF/25V X5R
C_{out}: 4 x 22uF 10V X7R
Ext 5V V_{BUS} Mux
reverse current blocking (490 mV drop)
+5V OK
Connect to use mux output.
Connect one but not both.
reverse current blocking (450mV drop)
DEFINES "DIRECT V_{OUT}"
Connect for direct to be ext VBUS
5V nominal, actual ~4.5V
Connect to directly use either buck V_{OUT} or ext. USB.
J5<->J4: +5V from mux, no other gang jumper needed J6<->J4: +5V is directly from buck output or ext. VBUS, depending on how other jumper is placed
